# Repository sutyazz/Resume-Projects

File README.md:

# Resume Projects Portfolio -- Branch

A comprehensive collection of engineering and computer science projects demonstrating expertise across multiple domains including embedded systems, web development, machine learning, signal processing, and hardware design.

## Table of Contents

1. [Digital Audio System FPGA](./Digital_Audio_System_FPGA_2023/)
2. [Class D Audio Amplifier](./Class_D_Audio_Amplifier_2023/)
3. [Machine Learning Optimized Flight Pathing](./Machine_Learning_Flight_Pathing_2025/)
4. [Machine Learning VR Project](./Machine_Learning_VR_Project_2024/)
5. [Autonomous Robot](./Autonomous_Robot_2025/)
6. [Autonomous Robot Web Project Summary](./Autonomous_Robot_Web_Project_Summary_2025/)
7. [Wearable PPG Sensor](./Wearable_PPG_Sensor_2024/)
8. [Dual-Wavelength Fiber Optic UART](./Dual_Wavelength_Fiber_Optic_UART_Report_2025/)
9. [mmWave Radar Processing](./mmWave_Radar_Processing_2024/)
10. [Network Latency Monitoring App](./Network_Latency_Monitoring_App_2024/)
11. [Personal Website & Daily Habit Tracker](./MyWebsite%20-%20WIP/)

---

## Projects Overview

### 🎛️ **Digital Audio & Signal Processing**
- **[Digital Audio System FPGA (2023)](./Digital_Audio_System_FPGA_2023/)** - Multi-feature digital audio synthesizer in Verilog with chord synthesis, ADSR modulation, and real-time effects
- **[Class D Audio Amplifier (2023)](./Class_D_Audio_Amplifier_2023/)** - High-efficiency Class D amplifier and speaker system design

### 🤖 **Machine Learning & Data Science**
- **[Machine Learning Optimized Flight Pathing (2025)](./Machine_Learning_Flight_Pathing_2025/)** - Python simulator using Monte Carlo sampling and Bayesian updating for eVTOL risk assessment
- **[Machine Learning VR Project (2024)](./Machine_Learning_VR_Project_2024/)** - Immersive VR experience integrating machine learning algorithms

### 🔌 **Embedded Systems & Robotics**
- **[Autonomous Robot (2025)](./Autonomous_Robot_2025/)** - Master-slave Arduino firmware with sensor fusion (ultrasonic, IR, IMU) and custom serial protocol
- **[Wearable PPG Sensor (2024)](./Wearable_PPG_Sensor_2024/)** - Biometric sensor PCB with Wi-Fi communication for real-time health monitoring

### 📡 **Communication Systems**
- **[Dual-Wavelength Fiber Optic UART (2025)](./Dual_Wavelength_Fiber_Optic_UART_Report_2025/)** - Full-duplex UART on single fiber using blue/IR LEDs with custom TIA/comparator circuits
- **[mmWave Radar Processing (2024)](./mmWave_Radar_Processing_2024/)** - Radar signal processing system for object detection and tracking

### 🌐 **Web Development & Networking**
- **[Network Latency Monitoring App (2024)](./Network_Latency_Monitoring_App_2024/)** - Flask-based web app for military network monitoring with C backend
- **[Autonomous Robot Web Project_Summary (2025)](./Autonomous_Robot_Web_Project_Summary_2025/)** - Comprehensive web documentation and Project_Summary
- **[Personal Website & Daily Habit Tracker (2023-2024)](./MyWebsite%20-%20WIP/)** - Full-stack personal web application combining photography portfolio with habit tracking system

## Technical Skills Demonstrated

- `**Programming Languages:** Python, C/C++, JavaScript, HTML/CSS, MATLAB, Verilog
- `**Frameworks & Libraries:** Flask, NumPy, Matplotlib, Pandas, SciPy
- `**Hardware & Embedded:** Arduino, PCB Design, FPGA, Sensor Integration, Digital Audio Processing
- `**Communication Protocols:** I²C, SPI, UART, TCP/UDP, Wi-Fi
- `**Signal Processing:** Digital filters, FFT, radar processing, optical communication, audio synthesis
- `**Machine Learning:** Monte Carlo methods, Bayesian updating, statistical analysis

## Project Reports

- **Dual_Wavelength_Fiber_Optic_UART_Report_2025.pdf** – Technical documentation of full-duplex fiber optic UART communication using dual-wavelength modulation and custom analog front-end circuits
- **Machine_Learning_Flight_Pathing_Report_2025.pdf** – Analysis and results of machine learning-based flight path optimization for eVTOL risk assessment
- **Machine_Learning_VR_Project_2024.pdf** – Overview and results of immersive VR project integrating machine learning algorithms
- **Wearable_PPG_Sensor_PCB_Instructions_2024.pdf** – Step-by-step guide for PCB design, assembly, and testing of a wearable PPG biometric sensor
- **Power_Electronics_ Flyback_Converter.pdf** – Design and analysis of a power electronics flyback converter system

## Contact & Links

Each project folder contains detailed documentation, source code, and implementation details. For questions or collaboration opportunities, please refer to individual project README files.

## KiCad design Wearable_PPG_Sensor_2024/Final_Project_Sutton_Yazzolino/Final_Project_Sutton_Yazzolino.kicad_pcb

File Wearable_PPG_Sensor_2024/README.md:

# Wearable PPG Sensor (2024)

## Project Overview
Developed a biometric sensor PCB with Wi-Fi communication for real-time photoplethysmography (PPG) data display and health monitoring.

## Skills Demonstrated
- **PCB Design**: Circuit design, layout, and fabrication
- **Embedded Programming**: Microcontroller firmware development
- **Communication Protocols**: I²C, SPI, Wi-Fi integration
- **Sensor Integration**: PPG sensor interfacing and calibration
- **Hardware Design**: Analog front-end design, power management
- **Wireless Communication**: Wi-Fi data transmission protocols

## Key Features
- Real-time PPG signal acquisition and processing
- Wi-Fi enabled for remote data monitoring
- Low-power wearable design
- Custom PCB with integrated sensors
- Real-time data visualization capabilities

## Technical Implementation
- Designed custom PCB with integrated PPG sensors
- Implemented I²C/SPI protocols for efficient sensor communication
- Developed Wi-Fi communication stack for real-time data transmission
- Created power management system for extended battery life
- Implemented signal processing algorithms for noise reduction

## Hardware Components
- Custom PCB design with integrated PPG sensors
- Microcontroller with Wi-Fi capabilities
- Power management circuitry
- Analog front-end for signal conditioning
- Battery management system

## Files
- `FINAL BOARD CODE/` - Production firmware
- `Final_Project_Sutton_Yazzolino/` - PCB design files and schematics
- `commands.jlink` - Programming and debugging scripts
- `ReFlash.bat` - Firmware update utilities

## Results
Successfully created a functional wearable PPG sensor with real-time Wi-Fi data transmission and accurate health monitoring capabilities.

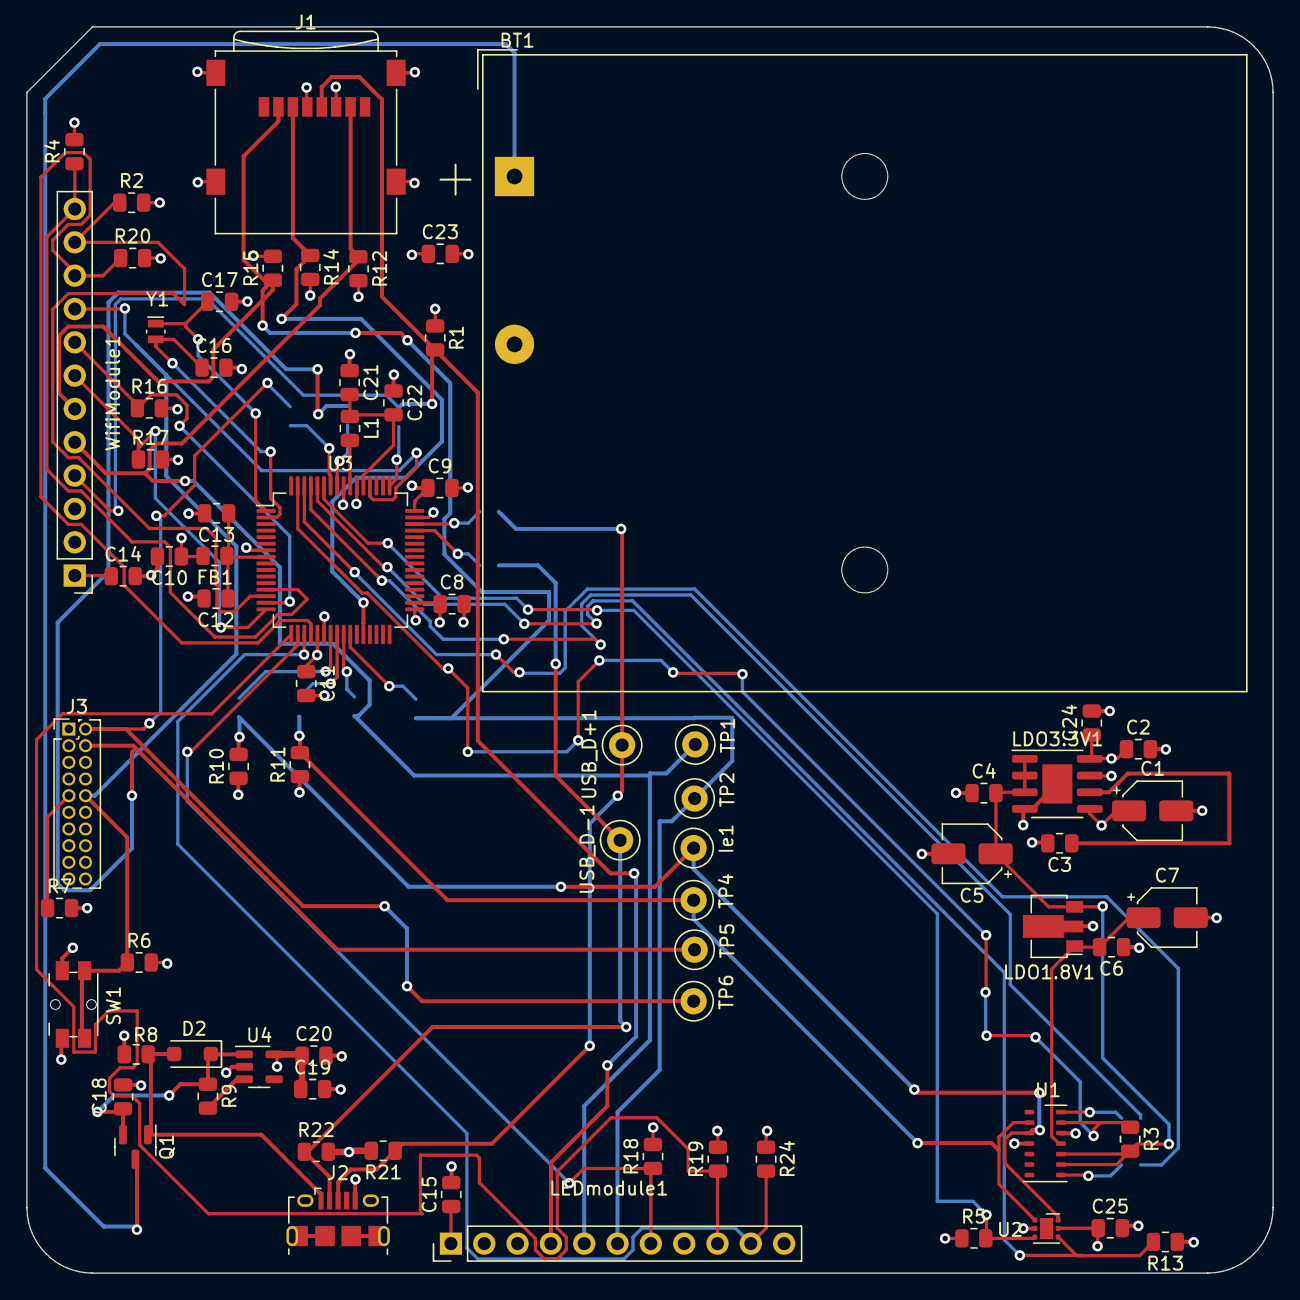
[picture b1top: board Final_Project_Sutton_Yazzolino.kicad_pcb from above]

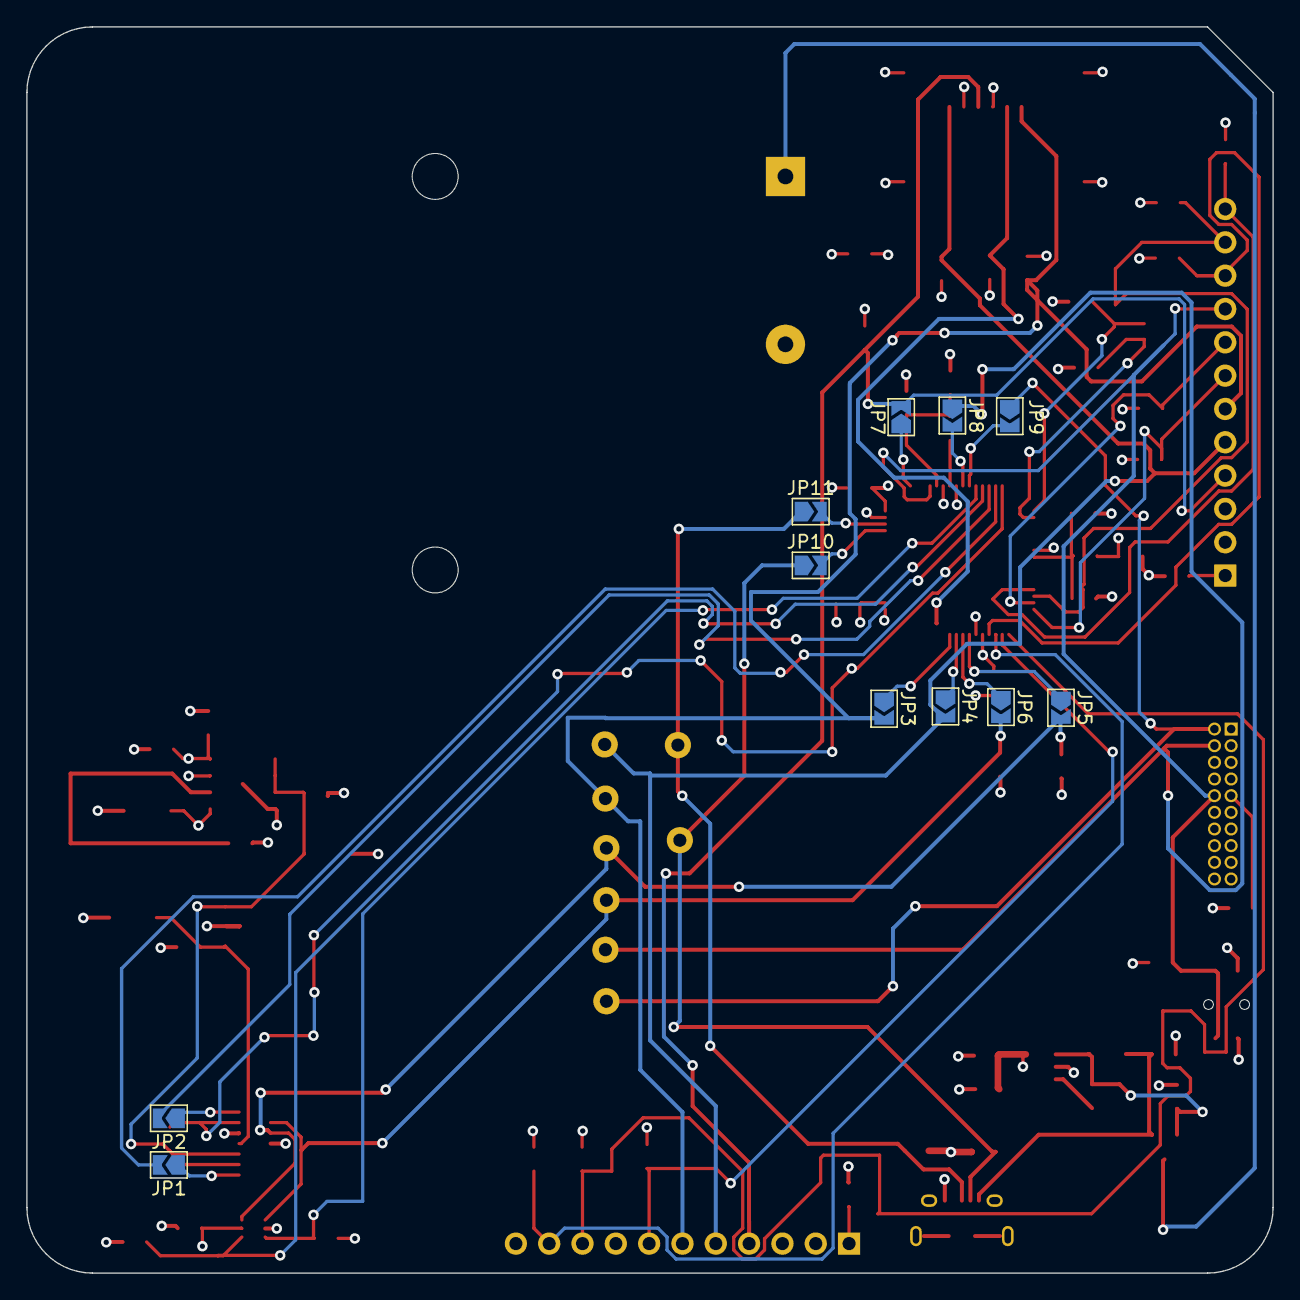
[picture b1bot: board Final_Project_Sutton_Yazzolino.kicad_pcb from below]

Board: 4 copper layers, 95.0 x 95.0 mm, 85 parts (11 on the bottom side), 50 nets.

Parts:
BT1: Battery; BatteryHolder_TruPower_BH-331P_3xAA
C1, C5, C7: 10uF; CP_Elec_4x3
C2, C4, C6: 100nF; R_0805_2012Metric
C3: 1nF; R_0805_2012Metric
C8, C9, C10, C11, C12, C14, C15, C23, C24, C25: 0.1uF; R_0805_2012Metric
C13, C18, C19, C22: 10uF; R_0805_2012Metric
C16, C17: 15pF; R_0805_2012Metric
C20, C21: 1uF; R_0805_2012Metric
D2: MBR1020VL; D_SOD-123F
FB1: FB - 30Ohm; R_0805_2012Metric
Ie1: TestPoint; TestPoint_Loop_D1.80mm_Drill1.0mm_Beaded
J1: Micro_SD_Card; microSD_HC_Wuerth_693072010801
J2: USB_B_Micro; USB_Micro-B_Amphenol_10118194_Horizontal
J3: Conn_ARM_JTAG_SWD_10; PinHeader_2x10_P1.27mm_Vertical
JP1, JP2, JP3, JP4, JP5, JP6, JP7, JP8, JP9, JP10, JP11: SolderJumper_2_Open; SolderJumper-2_P1.3mm_Open_TrianglePad1.0x1.5mm
L1: 10uH; R_0805_2012Metric
LDO1.8V1: AP130-18Y; SOT-89-3
LDO3.3V1: ADP7142ARDZ-3.3; SOIC-8-1EP_3.9x4.9mm_P1.27mm_EP2.29x3mm
LEDmodule1: Conn_01x11_Pin; PinHeader_1x11_P2.54mm_Vertical
Q1: IRLML5203; SOT-23
R1, R2, R4, R6, R7, R9, R10, R11, R13, R14, R16, R17, R18, R19, R20, R21, R22, R24: 10K; R_0805_2012Metric
R3: 4.7k; R_0805_2012Metric
R5, R12, R15: 10k; R_0805_2012Metric
R8: 100K; R_0805_2012Metric
SW1: SW_Push; Panasonic_EVQPUM_EVQPUD
TP1, TP2, TP4, TP5, TP6: TestPoint; TestPoint_Loop_D1.80mm_Drill1.0mm_Beaded
U1: MAX30102; Maxim_OLGA-14_3.3x5.6mm_P0.8mm
U2: TMP117; WSON-6-1EP_2x2mm_P0.65mm_EP1x1.6mm
U3: ATSAMD51J20A-A; TQFP-64_10x10mm_P0.5mm
U4: AP2112K-3.3; SOT-23-5
USB_D+1: TestPoint; TestPoint_Loop_D1.80mm_Drill1.0mm_Beaded
USB_D-1: TestPoint; TestPoint_Loop_D1.80mm_Drill1.0mm_Beaded
WifiModule1: Conn_01x12_Pin; PinHeader_1x12_P2.54mm_Vertical
Y1: 32.768kHz; Crystal_SMD_MicroCrystal_CM9V-T1A-2Pin_1.6x1.0mm

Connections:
+3.3V: C1.1, C2.1, C8.1, C9.1, C10.1, C11.1, C14.1, C15.1, C19.1, C20.1, C23.1, C24.1, C25.1, FB1.2, J1.4 (VDD), J3.1 (VTref), LDO3.3V1.5 (EN), LDO3.3V1.7 (VIN), LDO3.3V1.8 (VIN), LEDmodule1.1 (Vin), R1.1, R2.2, R4.2, R5.1, R6.2, R10.1, R11.1, R12.2, R14.2, R15.2, R16.2, R17.2, R18.2, R19.2, R20.2, R21.2, R22.2, R24.1, U2.5 (V+), U3.21 (VDDIOB), U3.34 (VDDIO), U3.48 (VDDIO), U3.56 (VDDIO), U4.5 (VOUT), WifiModule1.1 (Vin)
+BATT: BT1.1 (+), Q1.3 (D)
/I2C-CLK: JP6.2 (B), R11.2, TP4.1, U1.2 (SCL), U2.1 (SCL)
/I2C-DIO: Ie1.1, JP5.2 (B), R10.2, U1.3 (SDA), U2.6 (SDA)
/I2C-SWCLK: J3.4 (SWDCLK/TCK), JP8.1 (A), TP5.1
/I2C-SWDIO: J3.2 (SWDIO/TMS), JP9.1 (A), TP6.1
/LED_DC: LEDmodule1.9 (DC), R19.1, U3.17 (PA08)
/LED_SDCS: LEDmodule1.10 (SDCS), R24.2, U3.19 (PA10)
/LED_TFTCS: LEDmodule1.7 (TFTCS), R18.1, U3.18 (PA09)
/PulseOx_INT: R3.1, U1.13 (~INT), U3.63 (PB02)
/PulseOx_IRD: JP1.2 (B), U3.62 (PB01)
/PulseOx_RD: JP2.2 (B), U3.61 (PB00)
/SD_CMD: J1.3 (CMD), R14.1, U3.28 (PB15)
/SPI-CLK: J1.5 (CLK), JP7.2 (B), LEDmodule1.4 (SCK), R1.2, WifiModule1.4 (SCK)
/SPI_MISO: J1.7 (DAT0), JP4.2 (B), LEDmodule1.5 (MISO), R12.1, TP1.1, WifiModule1.5 (MISO)
/SPI_MOSI: J1.2 (DAT3/CD), JP3.2 (B), LEDmodule1.6 (MOSI), R15.1, TP2.1, WifiModule1.6 (MOSI)
/TempSensor_ADDR: R13.2, U2.4 (ADD0), U3.60 (PB31)
/TempSensor_INT: R5.2, U2.3 (ALERT), U3.59 (PB30)
/USB_D+: J2.3 (D+), JP11.1 (A), R21.1, USB_D+1.1
/USB_D-: J2.2 (D-), JP10.1 (A), R22.1, USB_D-1.1
/VDDA: C12.1, C13.1, FB1.1, U3.8 (VDDANA)
/Wifi_BUSY: R16.1, U3.15 (PA06), WifiModule1.8 (BUSY)
/Wifi_CS: R17.1, U3.16 (PA07), WifiModule1.7 (CS)
/Wifi_GPO: R20.1, U3.20 (PA11), WifiModule1.10 (GP0)
/Wifi_RXI: R2.1, U3.14 (PA05), WifiModule1.11 (RXI)
/Wifi_TXO: R4.1, U3.13 (PA04), WifiModule1.12 (TXO)
/reset: J3.10 (~RESET), R6.1, SW1.2, U3.52 (~RESET), WifiModule1.9 (RST)
GND: BT1.2 (-), C1.2, C2.2, C3.2, C4.1, C5.2, C6.1, C7.2, C8.2, C9.2, C10.2, C11.2, C12.2, C13.2, C14.2, C15.2, C16.2, C17.2, C18.1, C19.2, C20.2, C21.1, C22.1, C23.2, C24.2, C25.2, J1.6 (VSS), J1.9 (SHIELD), J2.5 (GND), J2.6 (Shield), J3.3 (GND), J3.5 (GND), LDO1.8V1.2 (GND), LDO3.3V1.4 (GND), LDO3.3V1.9 (GND), LEDmodule1.3 (GND), R7.2, R8.2, R13.1, SW1.1, U1.4 (PGND), U1.12 (GND), U2.2 (GND), U3.7 (GNDANA), U3.22 (GND), U3.33 (GND), U3.47 (GND), U3.54 (GND), U4.2 (GND), WifiModule1.3 (GND)
unnamed: C18.2, D2.1 (K), Q1.2 (S), R9.1, U4.1 (VIN)
unnamed: J3.9 (GNDDetect), R7.1
unnamed: JP1.1 (A), U1.8 (IR_DRV)
unnamed: JP2.1 (A), U1.14 (eR_DRV)
unnamed: JP3.1 (A), U3.26 (PB13)
unnamed: JP4.1 (A), U3.25 (PB12)
unnamed: JP5.1 (A), U3.23 (PB10)
unnamed: JP6.1 (A), U3.24 (PB11)
unnamed: JP7.1 (A), U3.49 (PB22)
unnamed: JP8.2 (B), U3.57 (PA30)
unnamed: JP9.2 (B), U3.58 (PA31)
unnamed: JP10.2 (B), U3.45 (PA24)
unnamed: JP11.2 (B), U3.46 (PA25)
unnamed: C4.2, C5.1, LDO1.8V1.3 (VI), LDO3.3V1.1 (VOUT), LDO3.3V1.2 (VOUT), LDO3.3V1.3 (SENSE/ADJ), R3.2, U1.9 (IR_LED+), U1.10 (eR_LED+)
unnamed: C6.2, C7.1, LDO1.8V1.1 (VO), U1.11 (VDD)
unnamed: C3.1, LDO3.3V1.6 (SS)
unnamed: C17.1, U3.1 (PA00), Y1.1
unnamed: C16.1, U3.2 (PA01), Y1.2
unnamed: C21.2, C22.2, L1.1, U3.53 (VDDCORE)
unnamed: L1.2, U3.55 (VSW)
unnamed: R9.2, U4.3 (EN)
VBUS: D2.2 (A), J2.1 (VBUS), Q1.1 (G), R8.1

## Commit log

2025-07-23 Razer Blade projects
    Uploading projects from old laptop for resume building
2025-07-23 Uploading More projects to consolidate
2025-07-23 wheresmario?
2025-07-23 lab reports
2025-07-23 Fixing Naming and ordering
2025-07-23 fixing naming
2025-07-23 dasda
    asdas
2025-07-23 asdsad
2025-07-23 Final Reordering
2025-07-23 merge with new README in FIBER OPTICS PROJECT
    as
2025-07-23 updates people, updates
2025-07-27 Create Resume-Projects.code-workspace
2025-08-18 SuttonLaptopLocal
